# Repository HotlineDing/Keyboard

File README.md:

This repo will contain the KiCad files used to desgin the keyboard.

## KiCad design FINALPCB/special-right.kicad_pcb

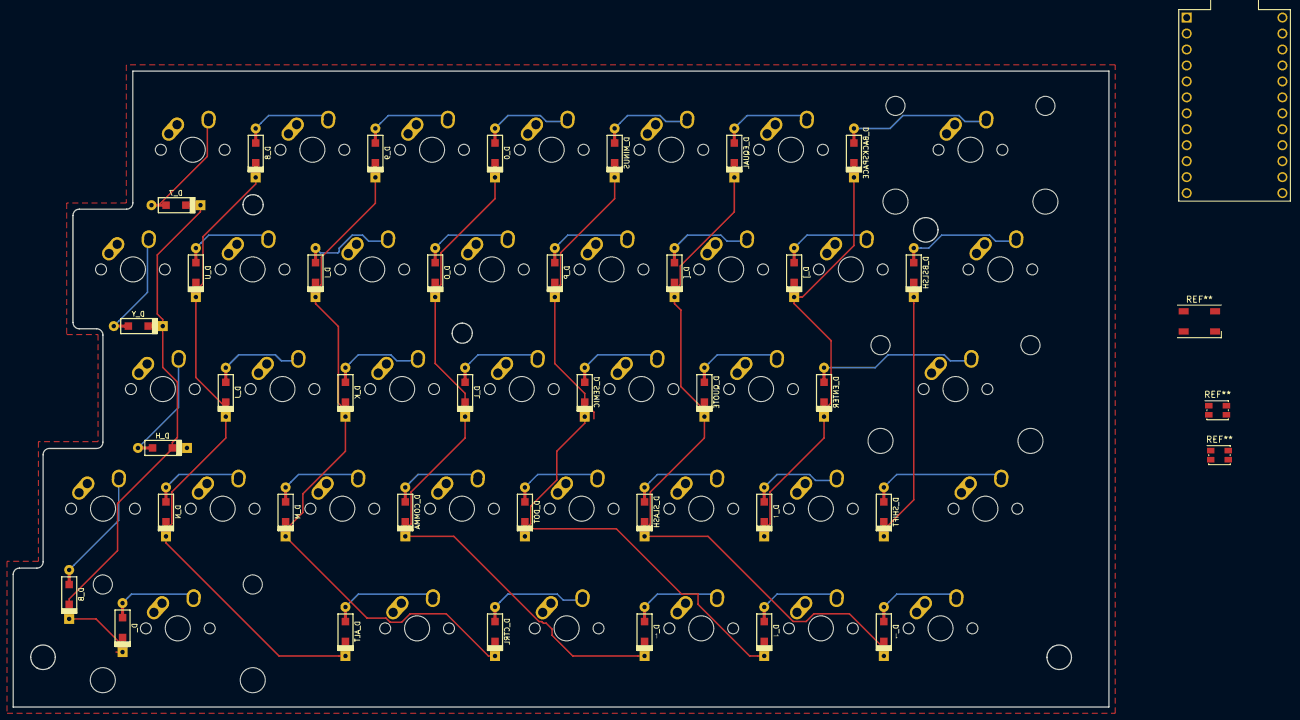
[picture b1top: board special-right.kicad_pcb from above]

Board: 2 copper layers, 174.5 x 101.2 mm, 72 parts (0 on the bottom side), 44 nets.

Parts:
D_, D_0, D_7, D_8, D_9: D; D_SOD123_axial
D_ALT: D; D_SOD123_axial
D_B: D; D_SOD123_axial
D_BACKSPACE: D; D_SOD123_axial
D_BSLSH: D; D_SOD123_axial
D_COMMA: D; D_SOD123_axial
D_CTRL: D; D_SOD123_axial
D_DOT: D; D_SOD123_axial
D_ENTER: D; D_SOD123_axial
D_EQUAL: D; D_SOD123_axial
D_H: D; D_SOD123_axial
D_I: D; D_SOD123_axial
D_J: D; D_SOD123_axial
D_K: D; D_SOD123_axial
D_L: D; D_SOD123_axial
D_M: D; D_SOD123_axial
D_MINUS: D; D_SOD123_axial
D_N: D; D_SOD123_axial
D_O: D; D_SOD123_axial
D_P: D; D_SOD123_axial
D_QUOTE: D; D_SOD123_axial
D_SEMIC: D; D_SOD123_axial
D_SHIFT: D; D_SOD123_axial
D_SLASH: D; D_SOD123_axial
D_U: D; D_SOD123_axial
D_Y: D; D_SOD123_axial
D_[: D; D_SOD123_axial
D_]: D; D_SOD123_axial
D_↼: D; D_SOD123_axial
D_↾: D; D_SOD123_axial
D_⇁: D; D_SOD123_axial
D_⇃: D; D_SOD123_axial
K_: KEYSW; MX-2.75U-NoLED
K_0, K_7, K_8, K_9: KEYSW; MX-1U-NoLED
K_ALT: KEYSW; MX-1.25U-NoLED
K_B: KEYSW; MX-1U-NoLED
K_BACKSPACE: KEYSW; MX-2U-NoLED
K_BSLSH: KEYSW; MX-1.5U-NoLED
K_COMMA: KEYSW; MX-1U-NoLED
K_CTRL: KEYSW; MX-1.25U-NoLED
K_DOT: KEYSW; MX-1U-NoLED
K_ENTER: KEYSW; MX-2.25U-NoLED
K_EQUAL: KEYSW; MX-1U-NoLED
K_H: KEYSW; MX-1U-NoLED
K_I: KEYSW; MX-1U-NoLED
K_J: KEYSW; MX-1U-NoLED
K_K: KEYSW; MX-1U-NoLED
K_L: KEYSW; MX-1U-NoLED
K_M: KEYSW; MX-1U-NoLED
K_MINUS: KEYSW; MX-1U-NoLED
K_N: KEYSW; MX-1U-NoLED
K_O: KEYSW; MX-1U-NoLED
K_P: KEYSW; MX-1U-NoLED
K_QUOTE: KEYSW; MX-1U-NoLED
K_SEMIC: KEYSW; MX-1U-NoLED
K_SHIFT: KEYSW; MX-1.75U-NoLED
K_SLASH: KEYSW; MX-1U-NoLED
K_U: KEYSW; MX-1U-NoLED
K_Y: KEYSW; MX-1U-NoLED
K_[: KEYSW; MX-1U-NoLED
K_]: KEYSW; MX-1U-NoLED
K_↼: KEYSW; MX-1U-NoLED
K_↾: KEYSW; MX-1U-NoLED
K_⇁: KEYSW; MX-1U-NoLED
K_⇃: KEYSW; MX-1U-NoLED

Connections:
/col0: D_.1, D_7.1, D_B.1, D_H.1, D_Y.1
/col1: D_8.1, D_ALT.1, D_J.1, D_N.1, D_U.1
/col2: D_9.1, D_CTRL.1, D_I.1, D_K.1, D_M.1
/col3: D_0.1, D_COMMA.1, D_L.1, D_O.1, D_↼.1
/col4: D_DOT.1, D_MINUS.1, D_P.1, D_SEMIC.1, D_⇃.1
/col5: D_EQUAL.1, D_QUOTE.1, D_SLASH.1, D_[.1, D_⇁.1
/col6: D_BACKSPACE.1, D_ENTER.1, D_].1, D_↾.1
/col7: D_BSLSH.1, D_SHIFT.1
unnamed: D_0.2, K_0.2
unnamed: D_7.2, K_7.2
unnamed: D_8.2, K_8.2
unnamed: D_9.2, K_9.2
unnamed: D_.2, K_.2
unnamed: D_ALT.2, K_ALT.2
unnamed: D_B.2, K_B.2
unnamed: D_BACKSPACE.2, K_BACKSPACE.2
unnamed: D_BSLSH.2, K_BSLSH.2
unnamed: D_COMMA.2, K_COMMA.2
unnamed: D_CTRL.2, K_CTRL.2
unnamed: D_DOT.2, K_DOT.2
unnamed: D_ENTER.2, K_ENTER.2
unnamed: D_EQUAL.2, K_EQUAL.2
unnamed: D_H.2, K_H.2
unnamed: D_I.2, K_I.2
unnamed: D_J.2, K_J.2
unnamed: D_K.2, K_K.2
unnamed: D_L.2, K_L.2
unnamed: D_M.2, K_M.2
unnamed: D_MINUS.2, K_MINUS.2
unnamed: D_N.2, K_N.2
unnamed: D_O.2, K_O.2
unnamed: D_P.2, K_P.2
unnamed: D_QUOTE.2, K_QUOTE.2
unnamed: D_SEMIC.2, K_SEMIC.2
unnamed: D_SHIFT.2, K_SHIFT.2
unnamed: D_SLASH.2, K_SLASH.2
unnamed: D_U.2, K_U.2
unnamed: D_Y.2, K_Y.2
unnamed: D_[.2, K_[.2
unnamed: D_].2, K_].2
unnamed: D_↼.2, K_↼.2
unnamed: D_↾.2, K_↾.2
unnamed: D_⇁.2, K_⇁.2
unnamed: D_⇃.2, K_⇃.2

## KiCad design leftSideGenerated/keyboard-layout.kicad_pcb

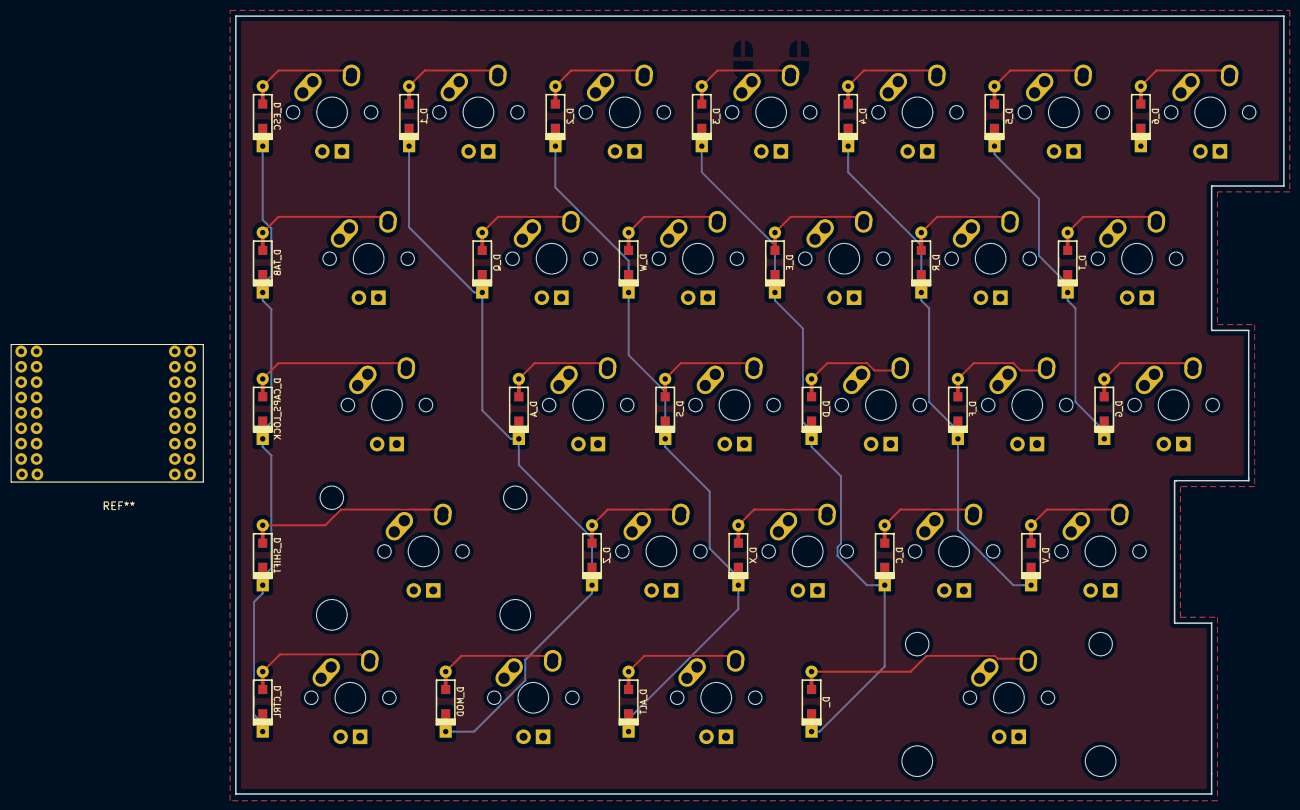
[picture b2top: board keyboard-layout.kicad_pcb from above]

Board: 2 copper layers, 136.4 x 101.2 mm, 56 parts (0 on the bottom side), 34 nets.

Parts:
D_, D_1, D_2, D_3, D_4, D_5, D_6: D; D_SOD123_axial
D_A: D; D_SOD123_axial
D_ALT: D; D_SOD123_axial
D_C: D; D_SOD123_axial
D_CAPS_LOCK: D; D_SOD123_axial
D_CTRL: D; D_SOD123_axial
D_D: D; D_SOD123_axial
D_E: D; D_SOD123_axial
D_ESC: D; D_SOD123_axial
D_F: D; D_SOD123_axial
D_G: D; D_SOD123_axial
D_MOD: D; D_SOD123_axial
D_Q: D; D_SOD123_axial
D_R: D; D_SOD123_axial
D_S: D; D_SOD123_axial
D_SHIFT: D; D_SOD123_axial
D_T: D; D_SOD123_axial
D_TAB: D; D_SOD123_axial
D_V: D; D_SOD123_axial
D_W: D; D_SOD123_axial
D_X: D; D_SOD123_axial
D_Z: D; D_SOD123_axial
K_: KEYSW; MX-2.75U-NoLED
K_1, K_2, K_3, K_4, K_5, K_6: KEYSW; MX-1U-NoLED
K_A: KEYSW; MX-1U-NoLED
K_ALT: KEYSW; MX-1.25U-NoLED
K_C: KEYSW; MX-1U-NoLED
K_CAPS_LOCK: KEYSW; MX-1.75U-NoLED
K_CTRL: KEYSW; MX-1.25U-NoLED
K_D: KEYSW; MX-1U-NoLED
K_E: KEYSW; MX-1U-NoLED
K_ESC: KEYSW; MX-1U-NoLED
K_F: KEYSW; MX-1U-NoLED
K_G: KEYSW; MX-1U-NoLED
K_MOD: KEYSW; MX-1.25U-NoLED
K_Q: KEYSW; MX-1U-NoLED
K_R: KEYSW; MX-1U-NoLED
K_S: KEYSW; MX-1U-NoLED
K_SHIFT: KEYSW; MX-2.25U-NoLED
K_T: KEYSW; MX-1U-NoLED
K_TAB: KEYSW; MX-1.5U-NoLED
K_V: KEYSW; MX-1U-NoLED
K_W: KEYSW; MX-1U-NoLED
K_X: KEYSW; MX-1U-NoLED
K_Z: KEYSW; MX-1U-NoLED

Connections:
/col0: D_CAPS_LOCK.1, D_CTRL.1, D_ESC.1, D_SHIFT.1, D_TAB.1
/col1: D_1.1, D_A.1, D_MOD.1, D_Q.1, D_Z.1
/col2: D_2.1, D_ALT.1, D_S.1, D_W.1, D_X.1
/col3: D_.1, D_3.1, D_C.1, D_D.1, D_E.1
/col4: D_4.1, D_F.1, D_R.1, D_V.1
/col5: D_5.1, D_G.1, D_T.1
unnamed: D_1.2, K_1.2
unnamed: D_2.2, K_2.2
unnamed: D_3.2, K_3.2
unnamed: D_4.2, K_4.2
unnamed: D_5.2, K_5.2
unnamed: D_6.2, K_6.2
unnamed: D_.2, K_.2
unnamed: D_A.2, K_A.2
unnamed: D_ALT.2, K_ALT.2
unnamed: D_C.2, K_C.2
unnamed: D_CAPS_LOCK.2, K_CAPS_LOCK.2
unnamed: D_CTRL.2, K_CTRL.2
unnamed: D_D.2, K_D.2
unnamed: D_E.2, K_E.2
unnamed: D_ESC.2, K_ESC.2
unnamed: D_F.2, K_F.2
unnamed: D_G.2, K_G.2
unnamed: D_MOD.2, K_MOD.2
unnamed: D_Q.2, K_Q.2
unnamed: D_R.2, K_R.2
unnamed: D_S.2, K_S.2
unnamed: D_SHIFT.2, K_SHIFT.2
unnamed: D_T.2, K_T.2
unnamed: D_TAB.2, K_TAB.2
unnamed: D_V.2, K_V.2
unnamed: D_W.2, K_W.2
unnamed: D_X.2, K_X.2
unnamed: D_Z.2, K_Z.2

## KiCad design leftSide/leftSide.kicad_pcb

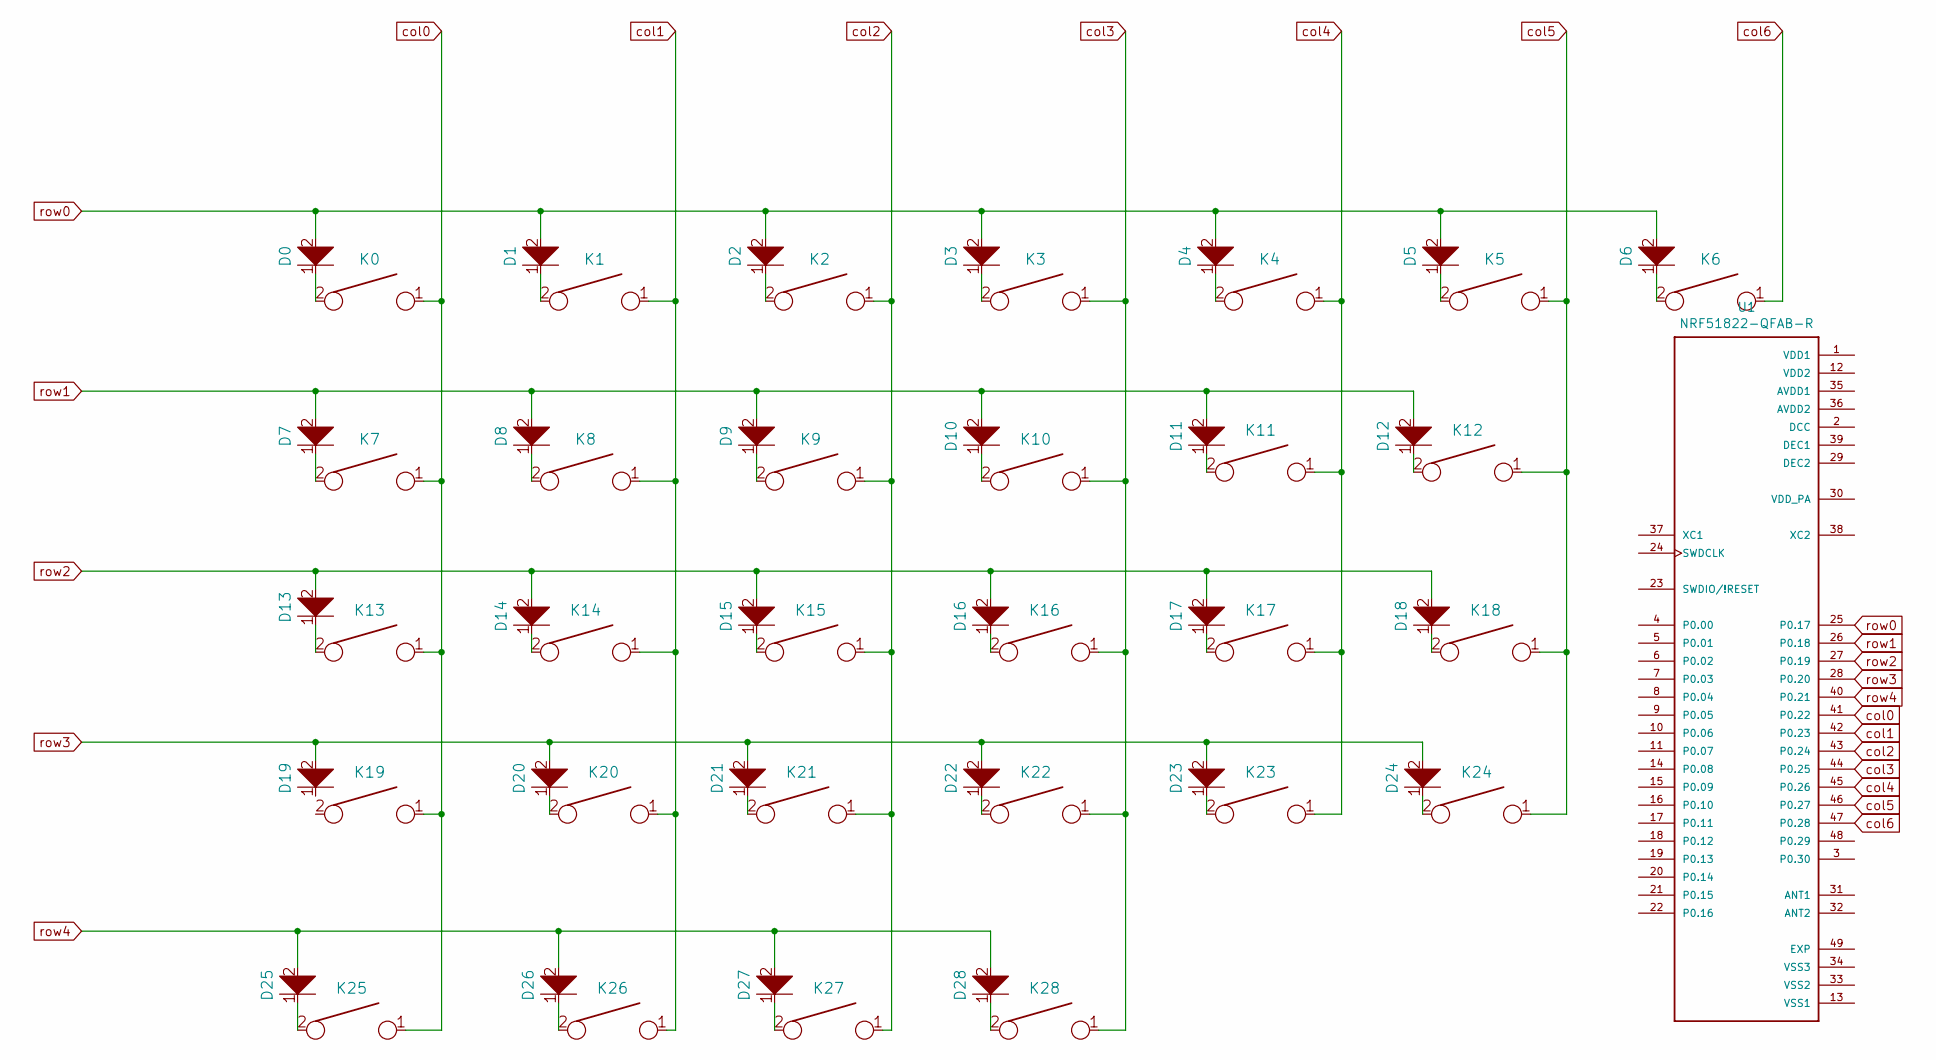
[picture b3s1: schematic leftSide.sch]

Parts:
D0, D1, D2, D3, D4, D5, D6, D7, D8, D9, D10, D11, D12, D13, D14, D15, D16, D17, D18, D19, D20, D21, D22, D23, D24, D25, D26, D27, D28: D; D_1806_4516Metric_Pad1.57x1.80mm_HandSolder
K0, K1, K2, K3, K4, K5, K6, K7, K8, K9, K10, K11, K12, K13, K14, K15, K16, K17, K18, K19, K20, K21, K22, K23, K24, K25, K26, K27, K28: KEYSW; Mx_Alps_100
U1: NRF51822-QFAB-R; QFN40P600X600X90-49N

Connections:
unnamed: D0.1, K0.2
unnamed: D1.1, K1.2
unnamed: D2.1, K2.2
unnamed: D3.1, K3.2
unnamed: D4.1, K4.2
unnamed: D5.1, K5.2
unnamed: D6.1, K6.2
unnamed: D7.1, K7.2
unnamed: D8.1, K8.2
unnamed: D9.1, K9.2
unnamed: D10.1, K10.2
unnamed: D11.1, K11.2
unnamed: D12.1, K12.2
unnamed: D13.1, K13.2
unnamed: D14.1, K14.2
unnamed: D15.1, K15.2
unnamed: D16.1, K16.2
unnamed: D17.1, K17.2
unnamed: D18.1, K18.2
unnamed: D20.1, K20.2
unnamed: D21.1, K21.2
unnamed: D22.1, K22.2
unnamed: D23.1, K23.2
unnamed: D24.1, K24.2
unnamed: D25.1, K25.2
unnamed: D26.1, K26.2
unnamed: D27.1, K27.2
unnamed: D28.1, K28.2
col0: K0.1, K7.1, K13.1, K19.1, K25.1, U1.41 (P0.22)
col1: K1.1, K8.1, K14.1, K20.1, K26.1, U1.42 (P0.23)
col2: K2.1, K9.1, K15.1, K21.1, K27.1, U1.43 (P0.24)
col3: K3.1, K10.1, K16.1, K22.1, K28.1, U1.44 (P0.25)
col4: K4.1, K11.1, K17.1, K23.1, U1.45 (P0.26)
col5: K5.1, K12.1, K18.1, K24.1, U1.46 (P0.27)
col6: K6.1, U1.47 (P0.28)
row0: D0.2, D1.2, D2.2, D3.2, D4.2, D5.2, D6.2, U1.25 (P0.17)
row1: D7.2, D8.2, D9.2, D10.2, D11.2, D12.2, U1.26 (P0.18)
row2: D13.2, D14.2, D15.2, D16.2, D17.2, D18.2, U1.27 (P0.19)
row3: D19.2, D20.2, D21.2, D22.2, D23.2, D24.2, U1.28 (P0.20)
row4: D25.2, D26.2, D27.2, D28.2, U1.40 (P0.21)

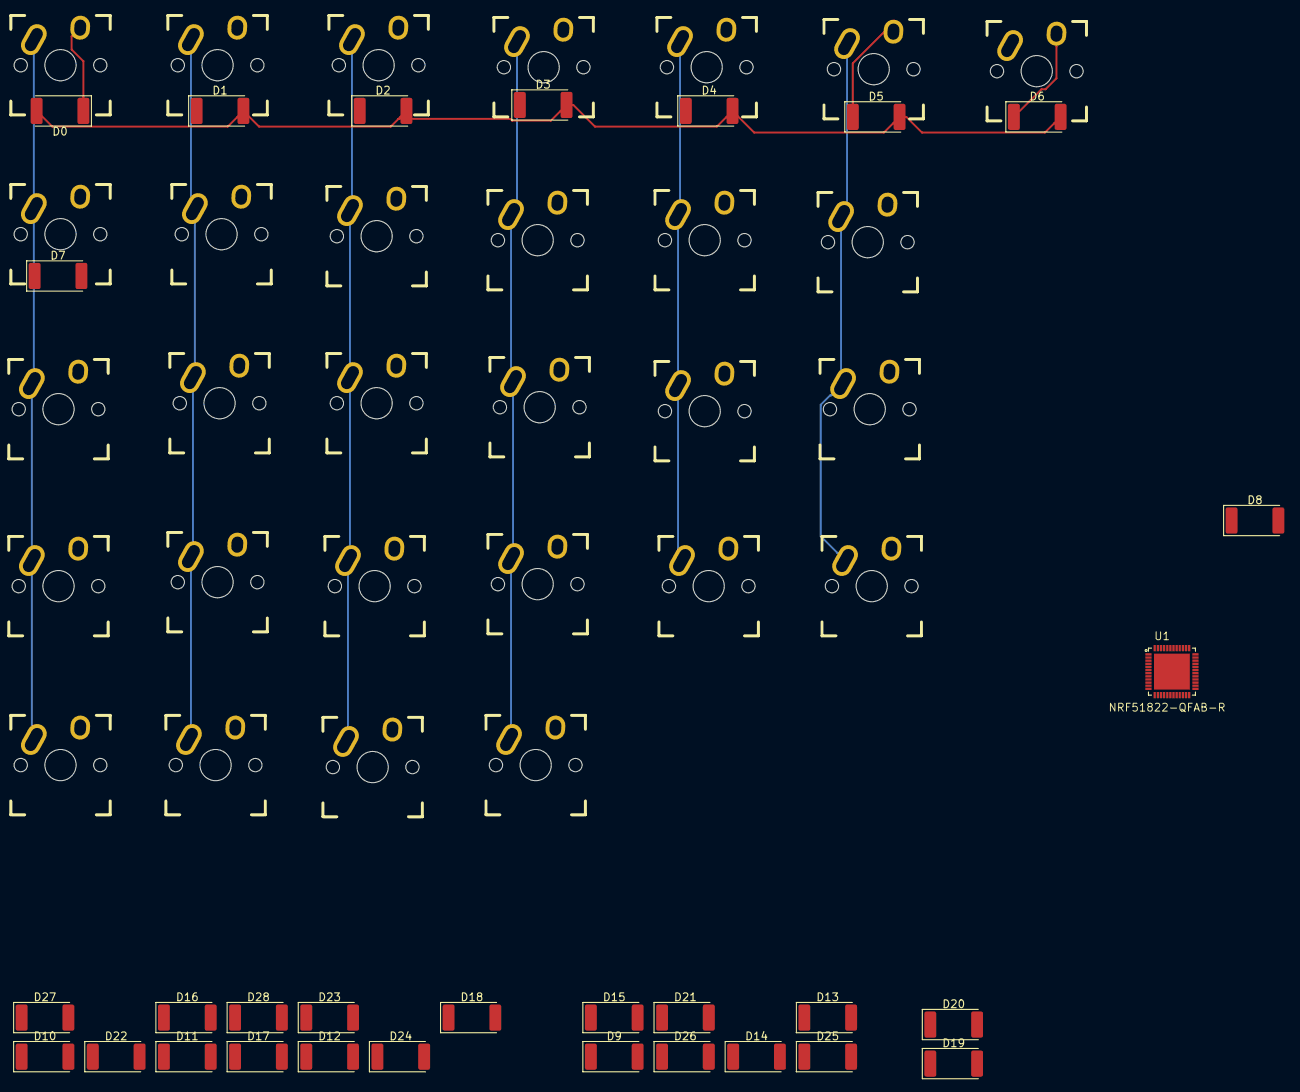
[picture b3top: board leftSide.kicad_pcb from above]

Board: 2 copper layers, 59 parts (0 on the bottom side), 40 nets.

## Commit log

2019-12-02 leftside almost done?
2020-03-05 shit ton of files
2020-03-05 too many folders
2020-03-12 FINAL ACRYLIC FILES
2020-03-13 done
2020-03-13 clean booiiii
2020-03-13 clean AF boooiiiii
2020-03-13 final case cutting done
2020-03-13 Needs engraving
2020-03-13 rip and done
2020-03-14 new files r2 cuts
2020-03-15 flip
2020-03-15 images
2020-03-15 new files
2020-03-15 more files
2020-03-16 usb cutout
2020-03-16 usb cutout and outline
